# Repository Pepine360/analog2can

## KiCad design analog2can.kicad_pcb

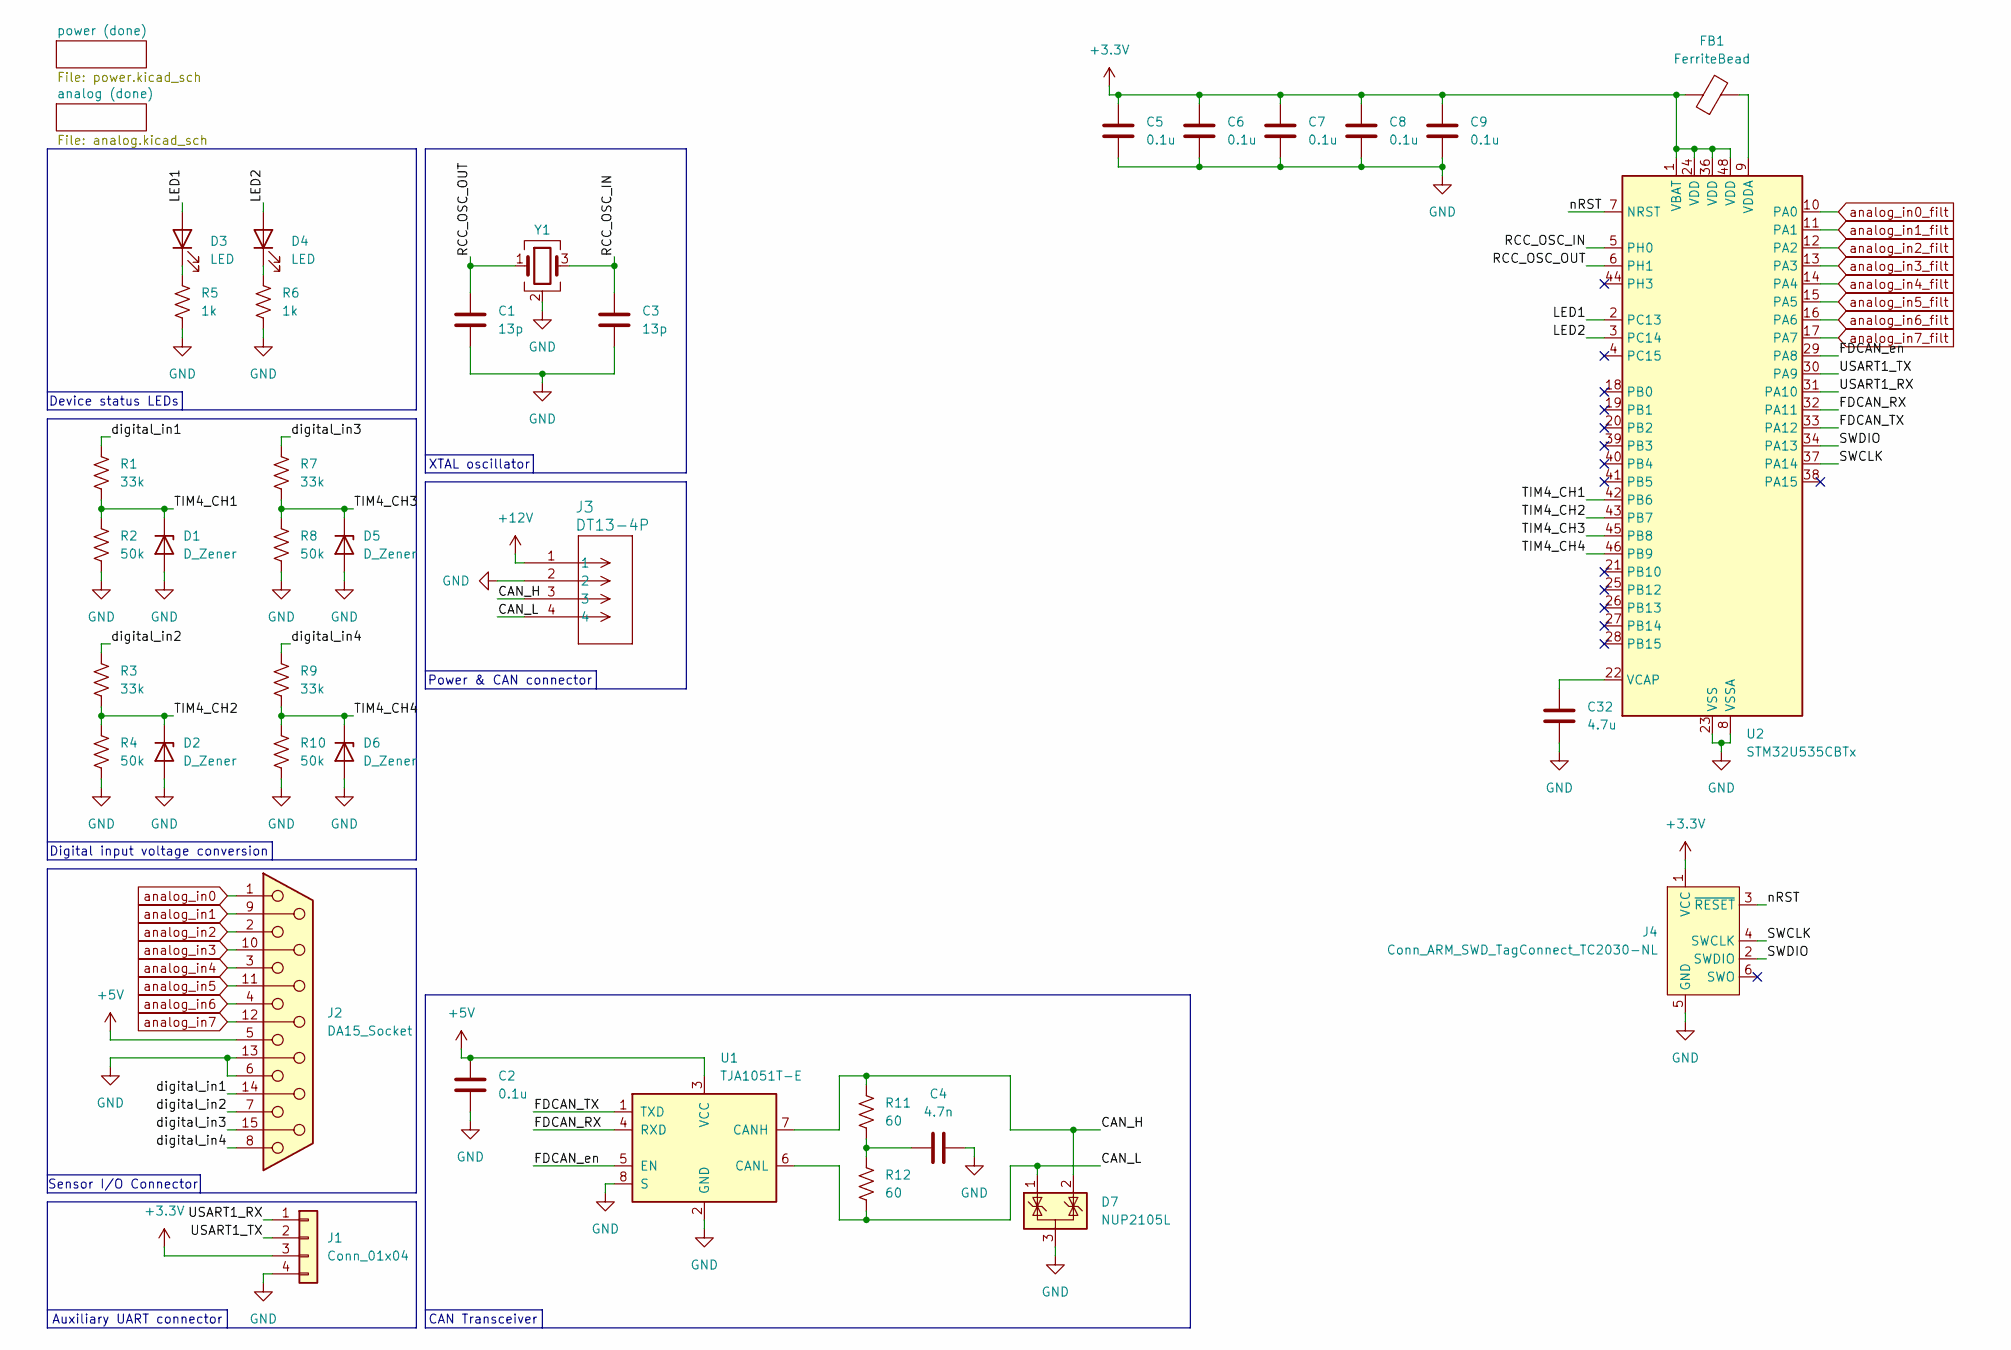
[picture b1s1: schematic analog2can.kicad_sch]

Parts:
C1, C3: 13p; C_0402_1005Metric_Pad0.74x0.62mm_HandSolder
C2, C5, C6, C7, C8, C9: 0.1u; C_0402_1005Metric_Pad0.74x0.62mm_HandSolder
C4: 4.7n; C_0402_1005Metric_Pad0.74x0.62mm_HandSolder
C32: 4.7u; C_0603_1608Metric_Pad1.08x0.95mm_HandSolder
D1, D2, D5, D6: D_Zener; D_SOD-323
D3, D4: LED; LED_0603_1608Metric_Pad1.05x0.95mm_HandSolder
D7: NUP2105L; SOT-23
FB1: FerriteBead; L_0402_1005Metric_Pad0.77x0.64mm_HandSolder
J1: Conn_01x04; Molex_KK-254_AE-6410-04A_1x04_P2.54mm_Vertical
J2: DA15_Socket; DSUB-15_Socket_Horizontal_P2.77x2.84mm_EdgePinOffset4.94mm_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
J3: DT13-4P; CONN4_DT13-4P_TEC
J4: Conn_ARM_SWD_TagConnect_TC2030-NL; Tag-Connect_TC2030-IDC-NL_2x03_P1.27mm_Vertical
R1, R3, R7, R9: 33k; R_0603_1608Metric_Pad0.98x0.95mm_HandSolder
R2, R4, R8, R10: 50k; R_0603_1608Metric_Pad0.98x0.95mm_HandSolder
R5, R6: 1k; R_0603_1608Metric_Pad0.98x0.95mm_HandSolder
R11, R12: 60; R_0603_1608Metric_Pad0.98x0.95mm_HandSolder
U1: TJA1051T-E; SOIC-8_3.9x4.9mm_P1.27mm
U2: STM32U535CBTx; LQFP-48_7x7mm_P0.5mm
Y1: ABM8-16.000MHZ-D1X-T; Crystal_SMD_Abracon_ABM8G-4Pin_3.2x2.5mm

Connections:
+3.3V: C5.1, C6.1, C7.1, C8.1, C9.1, FB1.1, J1.3, J4.1 (VCC), U2.1 (VBAT), U2.24 (VDD), U2.36 (VDD), U2.48 (VDD); also elsewhere on the board
+5V: C2.1, J2.5, U1.3 (VCC); also elsewhere on the board
+12V: J3.1; also elsewhere on the board
/CAN_H: D7.2 (K), J3.3, R11.1, U1.7 (CANH)
/CAN_L: D7.1 (K), J3.4, R12.2, U1.6 (CANL)
/FDCAN_RX: U1.4 (RXD), U2.32 (PA11)
/FDCAN_TX: U1.1 (TXD), U2.33 (PA12)
/FDCAN_en: U1.5 (EN), U2.29 (PA8)
/LED1: D3.2 (A), U2.2 (PC13)
/LED2: D4.2 (A), U2.3 (PC14)
/RCC_OSC_IN: C3.1, U2.5 (PH0), Y1.3
/RCC_OSC_OUT: C1.1, U2.6 (PH1), Y1.1
/SWCLK: J4.4 (SWCLK), U2.37 (PA14)
/SWDIO: J4.2 (SWDIO), U2.34 (PA13)
/TIM4_CH1: D1.1 (K), R1.2, R2.1, U2.42 (PB6)
/TIM4_CH2: D2.1 (K), R3.2, R4.1, U2.43 (PB7)
/TIM4_CH3: D5.1 (K), R7.2, R8.1, U2.45 (PB8)
/TIM4_CH4: D6.1 (K), R9.2, R10.1, U2.46 (PB9)
/USART1_RX: J1.1, U2.31 (PA10)
/USART1_TX: J1.2, U2.30 (PA9)
/digital_in1: J2.14, R1.1
/digital_in2: J2.7, R3.1
/digital_in3: J2.15, R7.1
/digital_in4: J2.8, R9.1
/nRST: J4.3 (~RESET), U2.7 (NRST)
GND: C1.2, C2.2, C3.2, C4.2, C5.2, C6.2, C7.2, C8.2, C9.2, C32.2, D1.2 (A), D2.2 (A), D5.2 (A), D6.2 (A), D7.3 (A), J1.4, J2.6, J2.13, J3.2, J4.5 (GND), R2.2, R4.2, R5.2, R6.2, R8.2, R10.2, U1.2 (GND), U1.8 (S), U2.8 (VSSA), U2.23 (VSS), U2.35 (VSS), U2.47 (VSS), Y1.2 (G), Y1.4 (G); also elsewhere on the board
unnamed: C4.1, R11.2, R12.1
unnamed: D3.1 (K), R5.1
unnamed: D4.1 (K), R6.1
unnamed: C32.1, U2.22 (VCAP)
unnamed: FB1.2, U2.9 (VDDA)
analog_in0: J2.1; also elsewhere on the board
analog_in0_filt: U2.10 (PA0); also elsewhere on the board
analog_in1: J2.9; also elsewhere on the board
analog_in1_filt: U2.11 (PA1); also elsewhere on the board
analog_in2: J2.2; also elsewhere on the board
analog_in2_filt: U2.12 (PA2); also elsewhere on the board
analog_in3: J2.10; also elsewhere on the board
analog_in3_filt: U2.13 (PA3); also elsewhere on the board
analog_in4: J2.3; also elsewhere on the board
analog_in4_filt: U2.14 (PA4); also elsewhere on the board
analog_in5: J2.11 (P111); also elsewhere on the board
analog_in5_filt: U2.15 (PA5); also elsewhere on the board
analog_in6: J2.4; also elsewhere on the board
analog_in6_filt: U2.16 (PA6); also elsewhere on the board
analog_in7: J2.12; also elsewhere on the board
analog_in7_filt: U2.17 (PA7); also elsewhere on the board

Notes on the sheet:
Device status LEDs
Power & CAN connector
Sensor I/O Connector
XTAL oscillator
CAN Transceiver
Digital input voltage conversion
Auxiliary UART connector

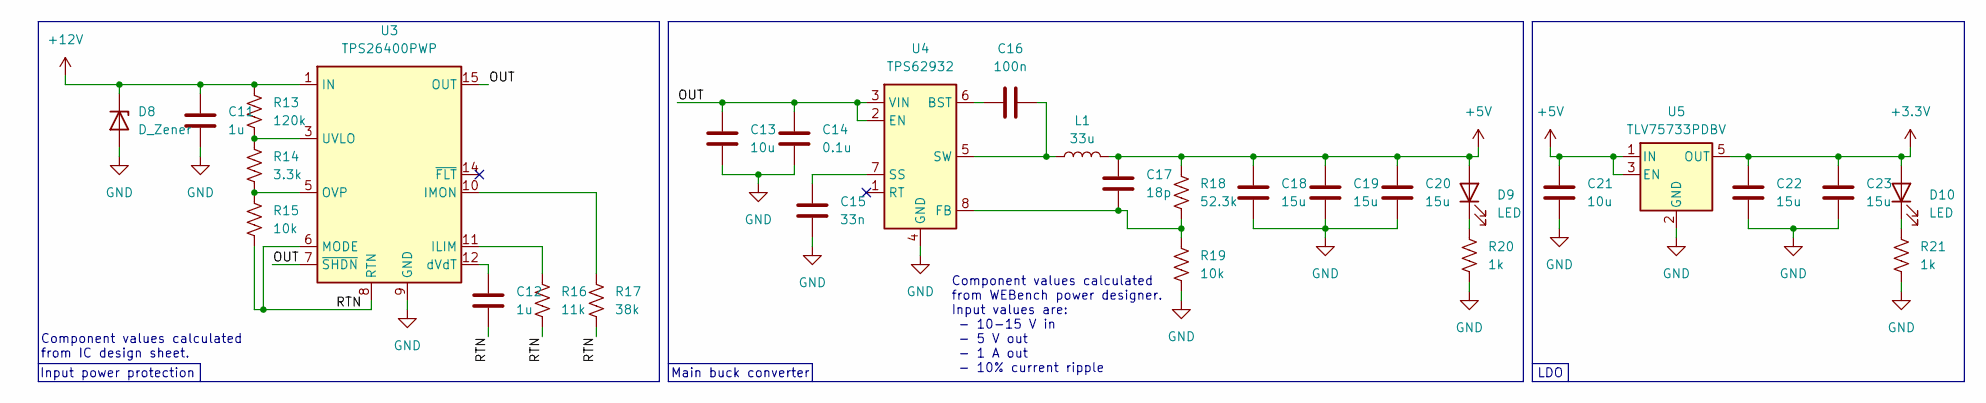
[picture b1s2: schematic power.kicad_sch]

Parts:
C11, C12: 1u; C_0603_1608Metric_Pad1.08x0.95mm_HandSolder
C13: 10u; LED_0805_2012Metric_Pad1.15x1.40mm_HandSolder
C14: 0.1u; C_0603_1608Metric_Pad1.08x0.95mm_HandSolder
C15: 33n; C_0402_1005Metric_Pad0.74x0.62mm_HandSolder
C16: 100n; C_0402_1005Metric_Pad0.74x0.62mm_HandSolder
C17: 18p; C_0402_1005Metric_Pad0.74x0.62mm_HandSolder
C18, C19, C20, C22, C23: 15u; C_0805_2012Metric_Pad1.18x1.45mm_HandSolder
C21: 10u; C_0805_2012Metric_Pad1.18x1.45mm_HandSolder
D8: D_Zener; D_SOD-523
D9, D10: LED; LED_0603_1608Metric_Pad1.05x0.95mm_HandSolder
L1: 33u; L_Coilcraft_XAL1510-333
R13: 120k; R_0603_1608Metric_Pad0.98x0.95mm_HandSolder
R14: 3.3k; R_0603_1608Metric_Pad0.98x0.95mm_HandSolder
R15, R19: 10k; R_0603_1608Metric_Pad0.98x0.95mm_HandSolder
R16: 11k; R_0603_1608Metric_Pad0.98x0.95mm_HandSolder
R17: 38k; R_0603_1608Metric_Pad0.98x0.95mm_HandSolder
R18: 52.3k; R_0603_1608Metric_Pad0.98x0.95mm_HandSolder
R20, R21: 1k; R_0603_1608Metric_Pad0.98x0.95mm_HandSolder
U3: TPS26400PWP; HTSSOP-16-1EP_4.4x5mm_P0.65mm_EP3.4x5mm_Mask2.66x2.46mm_The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
U4: TPS62932; SOT-583-8
U5: TLV75733PDBV; SOT-23-5

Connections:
+3.3V: C22.1, C23.1, D10.2 (A), U5.5 (OUT); also elsewhere on the board
+5V: C17.2, C18.1, C19.1, C20.1, C21.1, D9.2 (A), L1.2, R18.1, U5.1 (IN), U5.3 (EN); also elsewhere on the board
+12V: C11.1, D8.1 (K), R13.1, U3.1 (IN), U3.2 (IN); also elsewhere on the board
/power (done)/OUT: C13.1, C14.1, U3.7 (~SHDN), U3.15 (OUT), U3.16 (OUT), U4.2 (EN), U4.3 (VIN)
/power (done)/RTN: C12.2, R15.2, R16.2, R17.2, U3.6 (MODE), U3.8 (RTN), U3.17 (RTN)
GND: C11.2, C13.2, C14.2, C15.2, C18.2, C19.2, C20.2, C21.2, C22.2, C23.2, D8.2 (A), R19.2, R20.2, R21.2, U3.9 (GND), U4.4 (GND), U5.2 (GND); also elsewhere on the board
unnamed: D9.1 (K), R20.1
unnamed: D10.1 (K), R21.1
unnamed: R16.1, U3.11 (ILIM)
unnamed: R17.1, U3.10 (IMON)
unnamed: R14.2, R15.1, U3.5 (OVP)
unnamed: R13.2, R14.1, U3.3 (UVLO)
unnamed: C12.1, U3.12 (dVdT)
unnamed: C16.1, U4.6 (BST)
unnamed: C17.1, R18.2, R19.1, U4.8 (FB)
unnamed: C15.1, U4.7 (SS)
unnamed: C16.2, L1.1, U4.5 (SW)

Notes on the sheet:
Component values calculated from IC design sheet.
Main buck converter
LDO
Input power protection
Component values calculated from WEBench power designer. Input values are: - 10-15 V in - 5 V out - 1 A out - 10% current ripple

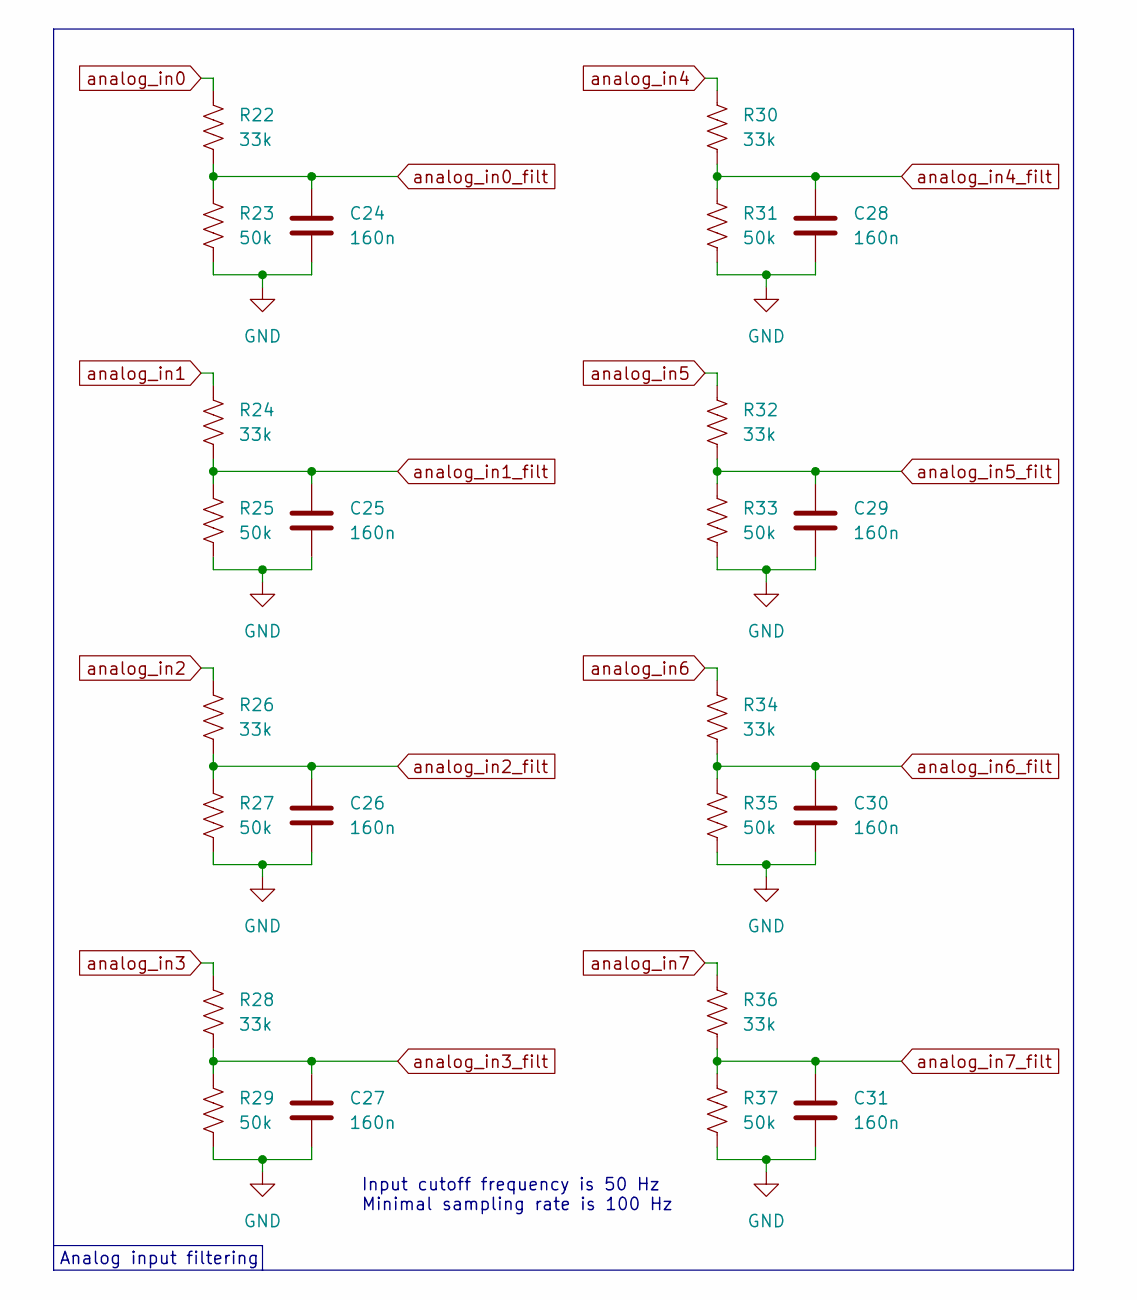
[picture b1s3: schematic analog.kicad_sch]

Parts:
C24, C25, C26, C27, C28, C29, C30, C31: 160n; C_0402_1005Metric_Pad0.74x0.62mm_HandSolder
R22, R24, R26, R28, R30, R32, R34, R36: 33k; R_0603_1608Metric_Pad0.98x0.95mm_HandSolder
R23, R25, R27, R29, R31, R33, R35, R37: 50k; R_0603_1608Metric_Pad0.98x0.95mm_HandSolder

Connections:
GND: C24.2, C25.2, C26.2, C27.2, C28.2, C29.2, C30.2, C31.2, R23.2, R25.2, R27.2, R29.2, R31.2, R33.2, R35.2, R37.2; also elsewhere on the board
analog_in0: R22.1; also elsewhere on the board
analog_in0_filt: C24.1, R22.2, R23.1; also elsewhere on the board
analog_in1: R24.1; also elsewhere on the board
analog_in1_filt: C25.1, R24.2, R25.1; also elsewhere on the board
analog_in2: R26.1; also elsewhere on the board
analog_in2_filt: C26.1, R26.2, R27.1; also elsewhere on the board
analog_in3: R28.1; also elsewhere on the board
analog_in3_filt: C27.1, R28.2, R29.1; also elsewhere on the board
analog_in4: R30.1; also elsewhere on the board
analog_in4_filt: C28.1, R30.2, R31.1; also elsewhere on the board
analog_in5: R32.1; also elsewhere on the board
analog_in5_filt: C29.1, R32.2, R33.1; also elsewhere on the board
analog_in6: R34.1; also elsewhere on the board
analog_in6_filt: C30.1, R34.2, R35.1; also elsewhere on the board
analog_in7: R36.1; also elsewhere on the board
analog_in7_filt: C31.1, R36.2, R37.1; also elsewhere on the board

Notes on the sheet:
Analog input filtering
Input cutoff frequency is 50 Hz Minimal sampling rate is 100 Hz

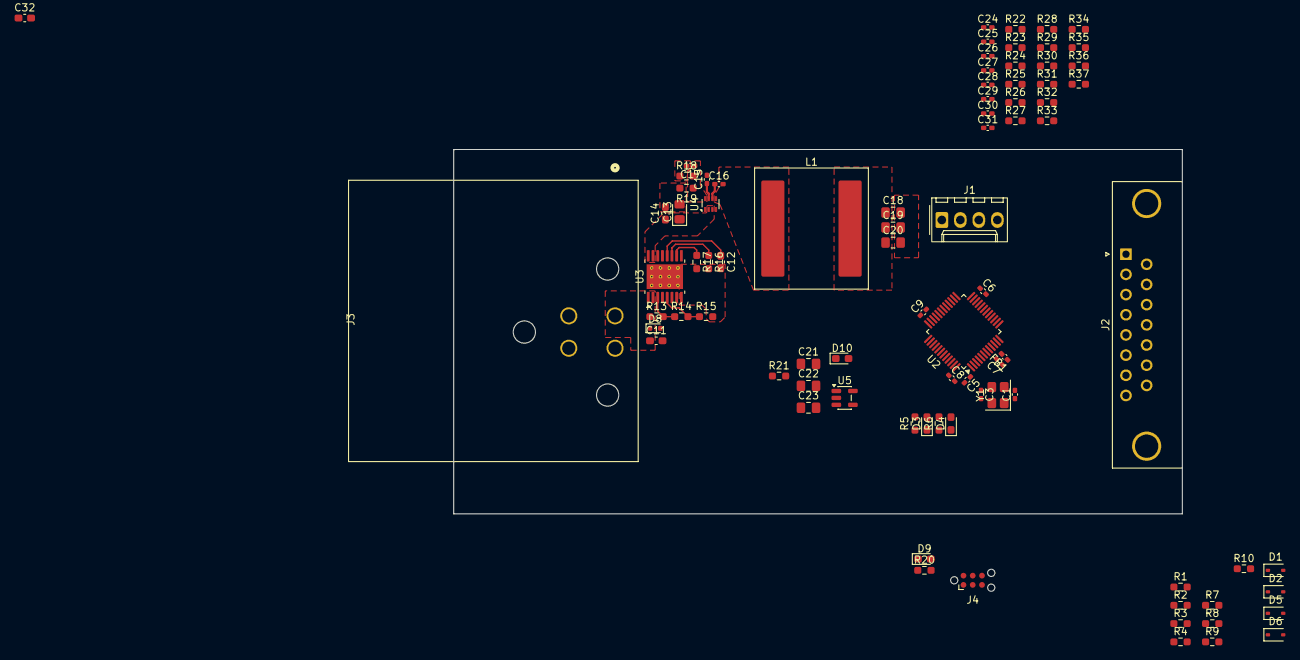
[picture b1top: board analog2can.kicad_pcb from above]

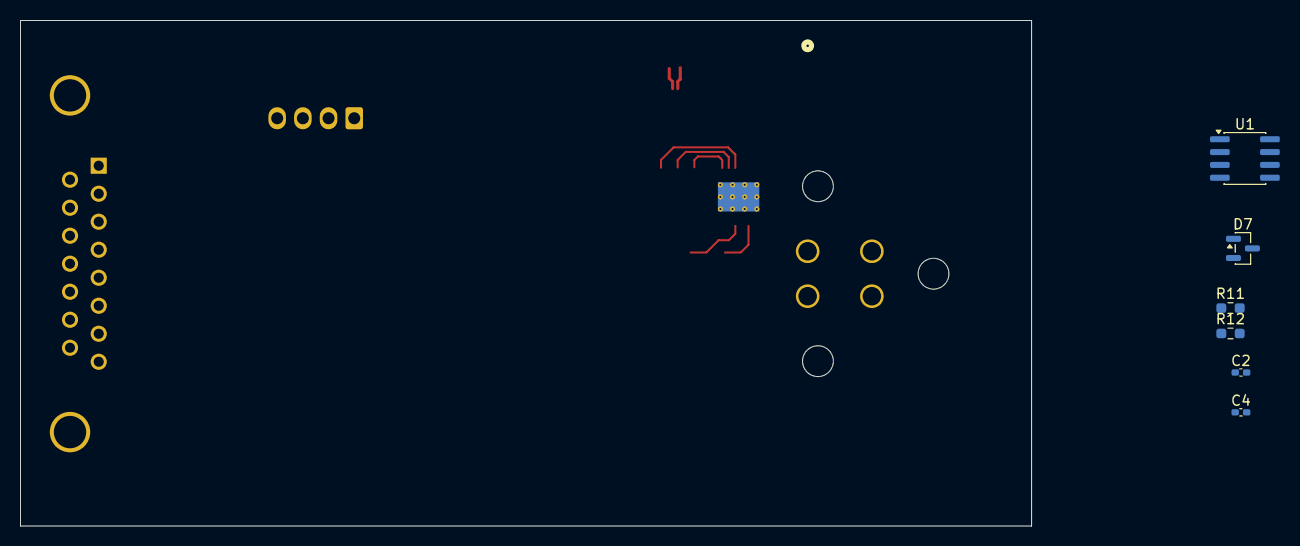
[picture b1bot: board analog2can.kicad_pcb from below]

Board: 4 copper layers, 100.0 x 50.0 mm, 90 parts (6 on the bottom side), 60 nets.

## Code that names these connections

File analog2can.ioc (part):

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Mcu.Name=STM32U535CBTx
Mcu.Package=LQFP48
Mcu.UserName=STM32U535CBTx
PA0.Mode=IN5-Single-Ended
PA0.Signal=ADC1_IN5
PA1.Mode=IN6-Single-Ended
PA1.Signal=ADC1_IN6
PA10.Mode=Asynchronous
PA10.Signal=USART1_RX
PA11.Mode=FDCAN_Activate
PA11.Signal=FDCAN1_RX
PA12.Mode=FDCAN_Activate
PA12.Signal=FDCAN1_TX
PA13\ (JTMS/SWDIO).Mode=Serial_Wire
PA13\ (JTMS/SWDIO).Signal=DEBUG_JTMS-SWDIO
PA14\ (JTCK/SWCLK).Mode=Serial_Wire
PA14\ (JTCK/SWCLK).Signal=DEBUG_JTCK-SWCLK
PA2.Mode=IN7-Single-Ended
PA2.Signal=ADC1_IN7
PA3.Mode=IN8-Single-Ended
PA3.Signal=ADC1_IN8
PA4.Mode=IN9-Single-Ended
PA4.Signal=ADC1_IN9
PA5.Mode=IN10-Single-Ended
PA5.Signal=ADC1_IN10
PA6.Mode=IN11-Single-Ended
PA6.Signal=ADC1_IN11
PA7.Mode=IN12-Single-Ended
PA7.Signal=ADC1_IN12
PA8.Signal=GPIO_Output
PA9.Mode=Asynchronous
PA9.Signal=USART1_TX
PB6.Signal=S_TIM4_CH1
PB7.Signal=S_TIM4_CH2
PB8.Signal=S_TIM4_CH3
PB9.Signal=S_TIM4_CH4
PC13.Signal=GPIO_Output
PC14-OSC32_IN\ (PC14).Signal=GPIO_Output
PH0-OSC_IN\ (PH0).Mode=HSE-External-Oscillator
PH0-OSC_IN\ (PH0).Signal=RCC_OSC_IN
PH1-OSC_OUT\ (PH1).Mode=HSE-External-Oscillator
PH1-OSC_OUT\ (PH1).Signal=RCC_OSC_OUT
RCC.HSE_VALUE=16000000
board=custom
